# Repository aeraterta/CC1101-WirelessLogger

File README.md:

# Wireless Data Logging Platform for Human Temperature and Pulse Rate with Networked Mobile Nodes

<p align="center">

<p>

This is an undergraduate thesis made by Anthony E. Raterta as a requirement for the Degree Bachelor of Science in Electronics and Communications Engineering. 

## Objectives

Generally, the main objective of this study is to construct a prototype of a wireless multi-node data logger that has mobile sensor nodes using transceivers that communicate in the ISM band.

The following are the specific objectives of this study:

1.	To construct a wearable data logger platform.
2.	To utilize the CC1101 transceiver chips for communication.
3.	To attach a temperature and pulse rate sensor in the data logger platform for monitoring human body temperature and pulse rate. 
4.	To identify a suitable location for human body temperature and pulse rate monitoring.

## Methods 

### Flow

The operation of the system imposed is shown in the image below. It contains simplified illustration of the two major parts, the mobile sensor node which may be of any number but for the study, the researcher only made two nodes. The other major part of the system is the receiver node which receives the packets sent by both sensor nodes and dummy nodes.

<p align="center">

<p>

### Block Diagram

Shown in the image below is the physical architecture of the system designed to gather temperature and pulse rate of a patient at an interval set. A single sensor node is composed of an MLX90614 infrared thermometer and an infrared based Grove ear-clip pulse rate sensor.  These modules serve as input devices to an ATmega328p microcontroller unit with a CC1101 RF transceiver working at 433 mega hertz frequency band connected into it and to have the data gathered transmitted into the receiver node which is composed of a CC1101 RF transceiver, an Arduino UNO and a personal computer or a laptop. The microcontroller unit serves as a bridge to have the gathered data stored into the PC or the database pool.

<p align="center">

<p>

### Materials:

1. MCU - For the device, a programmable ATmega328p microcontroller will be used to do the tasks set. The circuit of an Arduino UNO will be used since its circuit is free and its programming IDE is open source. Also, several supports and forums are available online which would be a great help for the study and could minimize the period of the over-all development process. However, some parts of the Arduino UNO are not usable for the hardware design and may be deemed unnecessary so these parts will be disregarded. Also, the ATmega328p working at 3.3 volts  in the Arduino UNO can also be set to use its internal 8 MHz clock which could be a great option in the aim of minimizing the size of the output device.

2. [MLX90614 Infrared Thermometer](https://www.melexis.com/en/documents/documentation/datasheets/datasheet-mlx90614) - A non-contact MLX90614 Infrared Thermometer working at voltage range of 2.4 – 3.6 volts will be used for the sensor node to gather temperature in degrees Celsius (°C). MLX90614 is best in medical usage with an accuracy of 0.5 degrees Celsius (°C).

3. [Grove Ear-Clip Heart Pulse Sensor](https://wiki.seeedstudio.com/Grove-Ear-clip_Heart_Rate_Sensor/) - The Grove ear-clip pulse sensor is an infrared based sensor that could detect the changes in the density of blood due to the occurrence of pulse during blood circulations. By determining the time interval of the changes of the blood density in the ear lobe, the sensor can have an accurate value of pulse rate.

4. [CC1101 RF Transceiver](http://www.ti.com/lit/ds/symlink/cc1101.pdf?ts=1590260097931) - To maximize the mobility of the sensor node, the transmission of the data gathered from the sensors can be sent wirelessly depending on the choice of media. The effective transmission range for such media should also be maximized so that a bigger scope of a network will be made without jeopardizing the aim of minimizing the power consumption of each component used in the device. To cater such considerations, a CC1101 RF transceiver operating at 433 MHz was used. The said transceiver is capable of naming each node with a specific unique address which is beneficial for the study. A CC1101 RF transceiver break-out module will be used in the early development of the device for testing and debugging purposes. 

5. [Power Supply](https://github.com/aeraterta/CC1101-WirelessLogger/tree/master/Design/ADI-sepic-boost-converter) - The devices uses the ADP1621 SEPIC Converter which supplies a constant 3.3 volts output despite the diminishing value of input voltage ranging from 5 – 3 volts. Such circuit is ideal for mobile data loggers because of its capability of regulating and boosting input voltages.

6. Power Source - Since the main power supply needed for the device needs input voltage ranging from 3 to 5 volts, a mobile phone battery is a good option for such application. 

## Device

### PCB Layout Plan

<p align="center">

<p>

### PCB Layout vs Actual

###### Mobile Node

<p align="center">

<p>

###### Receiver Node

<p align="center">

<p>

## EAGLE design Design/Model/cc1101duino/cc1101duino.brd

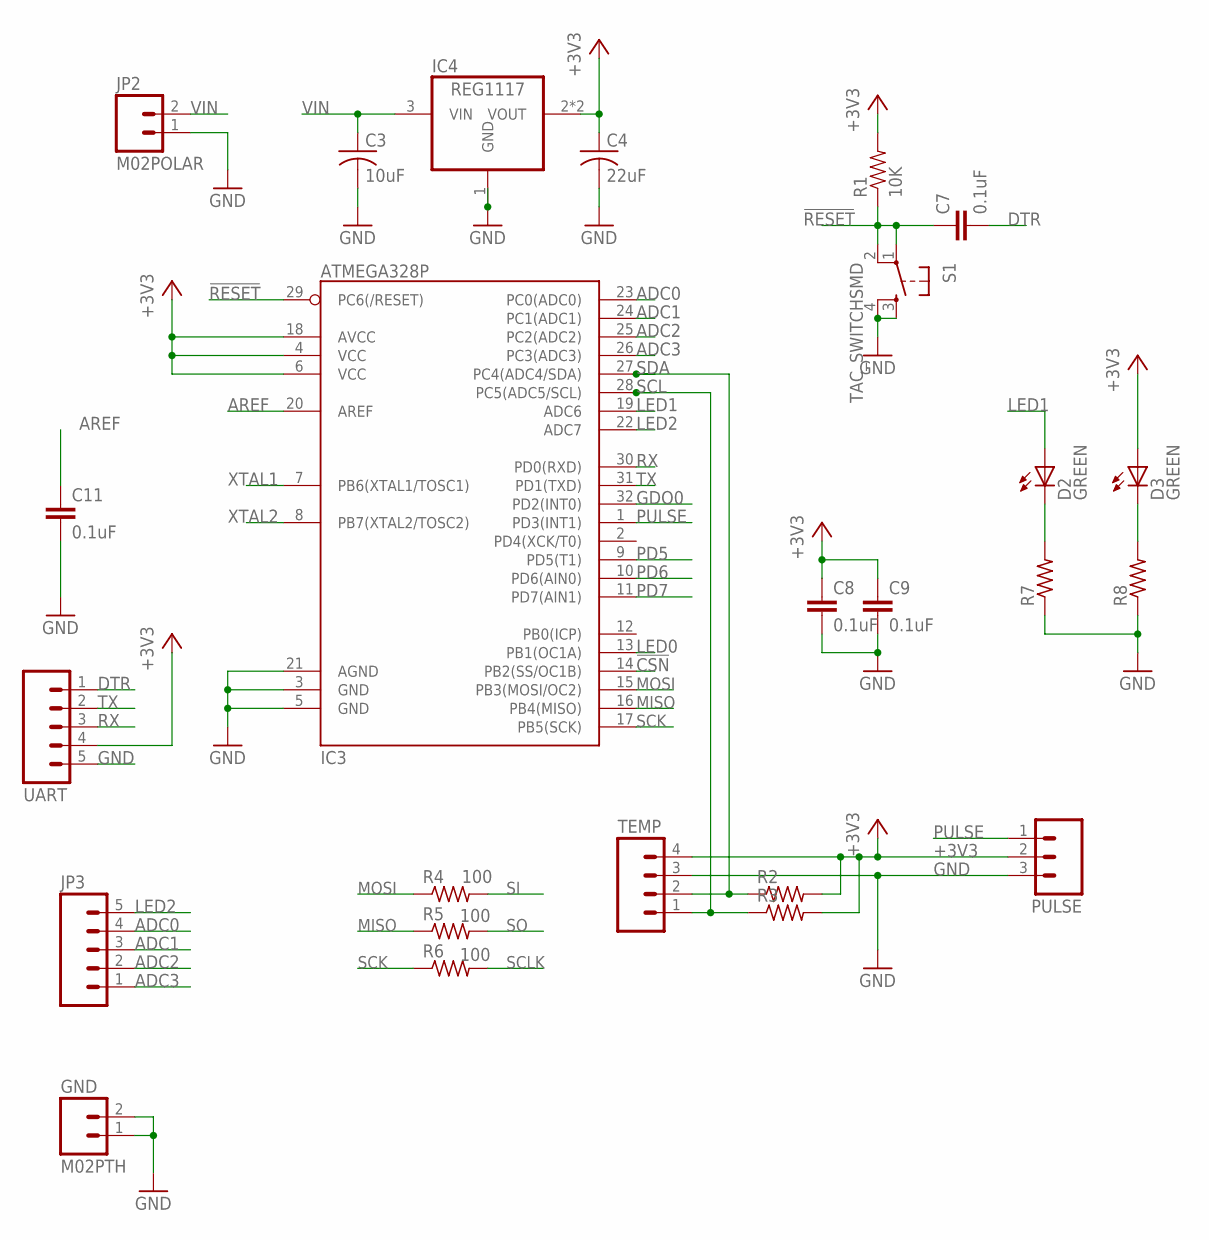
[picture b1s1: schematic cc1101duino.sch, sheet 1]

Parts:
C3: 10uF; C0805; MPN 06034D106MAT2A
C4: 22uF; C0805; MPN 06034D106MAT2A
C7, C8, C9, C11: 0.1uF; 0805
D2, D3: GREEN; LED-0603
GND: M02PTH; 1X02
IC3: ATMEGA328P; TQFP32-08
IC4: REG1117; SOT223
JP2: M02POLAR; MOLEX-1X2
JP3: M05PTH; 1X05
PULSE: M03POLAR; MOLEX-1X3
R1: 10K; 0603-RES
R2, R3: R-US_R0805; R0805
R4, R5, R6: 100; R0603
R7, R8: R-US_R0603; R0603
S1: TAC_SWITCHSMD; TACTILE-SWITCH-SMD
TEMP: M04POLAR; MOLEX-1X4
UART: M05PTH; 1X05

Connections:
!CSN: IC3.14 (PB2(SS/OC1B)); also elsewhere on the board
!RESET: C7.1, IC3.29 (PC6(/RESET)), R1.1, S1.1, S1.2
+3V3: C4.1, C8.1, C9.1, D3.A, IC3.4 (VCC), IC3.6 (VCC), IC3.18 (AVCC), IC4.2 (VOUT), IC4.4 (VOUT), PULSE.2, R1.2, R2.2, R3.2, TEMP.4, UART.4; also elsewhere on the board
ADC0: IC3.23 (PC0(ADC0)), JP3.4
ADC1: IC3.24 (PC1(ADC1)), JP3.3
ADC2: IC3.25 (PC2(ADC2)), JP3.2
ADC3: IC3.26 (PC3(ADC3)), JP3.1
AREF: C11.1, IC3.20 (AREF)
DTR: C7.2, UART.1
GDO0: IC3.32 (PD2(INT0)); also elsewhere on the board
GND: C3.2, C4.2, C8.2, C9.2, C11.2, GND.1, GND.2, IC3.3 (GND), IC3.5 (GND), IC3.21 (AGND), IC4.1 (GND), JP2.1, PULSE.3, R7.1, R8.1, S1.3, S1.4, TEMP.3, UART.5; also elsewhere on the board
LED0: IC3.13 (PB1(OC1A))
LED1: D2.A, IC3.19 (ADC6)
LED2: IC3.22 (ADC7), JP3.5
MISO: IC3.16 (PB4(MISO)), R5.1; also elsewhere on the board
MOSI: IC3.15 (PB3(MOSI/OC2)), R4.1; also elsewhere on the board
unnamed: D2.C, R7.2
unnamed: D3.C, R8.2
PD5: IC3.9 (PD5(T1))
PD6: IC3.10 (PD6(AIN0))
PD7: IC3.11 (PD7(AIN1))
PULSE: IC3.1 (PD3(INT1)), PULSE.1
RX: IC3.30 (PD0(RXD)), UART.3
SCK: IC3.17 (PB5(SCK)), R6.1; also elsewhere on the board
SCL: IC3.28 (PC5(ADC5/SCL)), R3.1, TEMP.1
SCLK: R6.2; also elsewhere on the board
SDA: IC3.27 (PC4(ADC4/SDA)), R2.1, TEMP.2
SI: R4.2; also elsewhere on the board
SO: R5.2; also elsewhere on the board
TX: IC3.31 (PD1(TXD)), UART.2
VIN: C3.1, IC4.3 (VIN), JP2.2
XTAL1: IC3.7 (PB6(XTAL1/TOSC1))
XTAL2: IC3.8 (PB7(XTAL2/TOSC2))

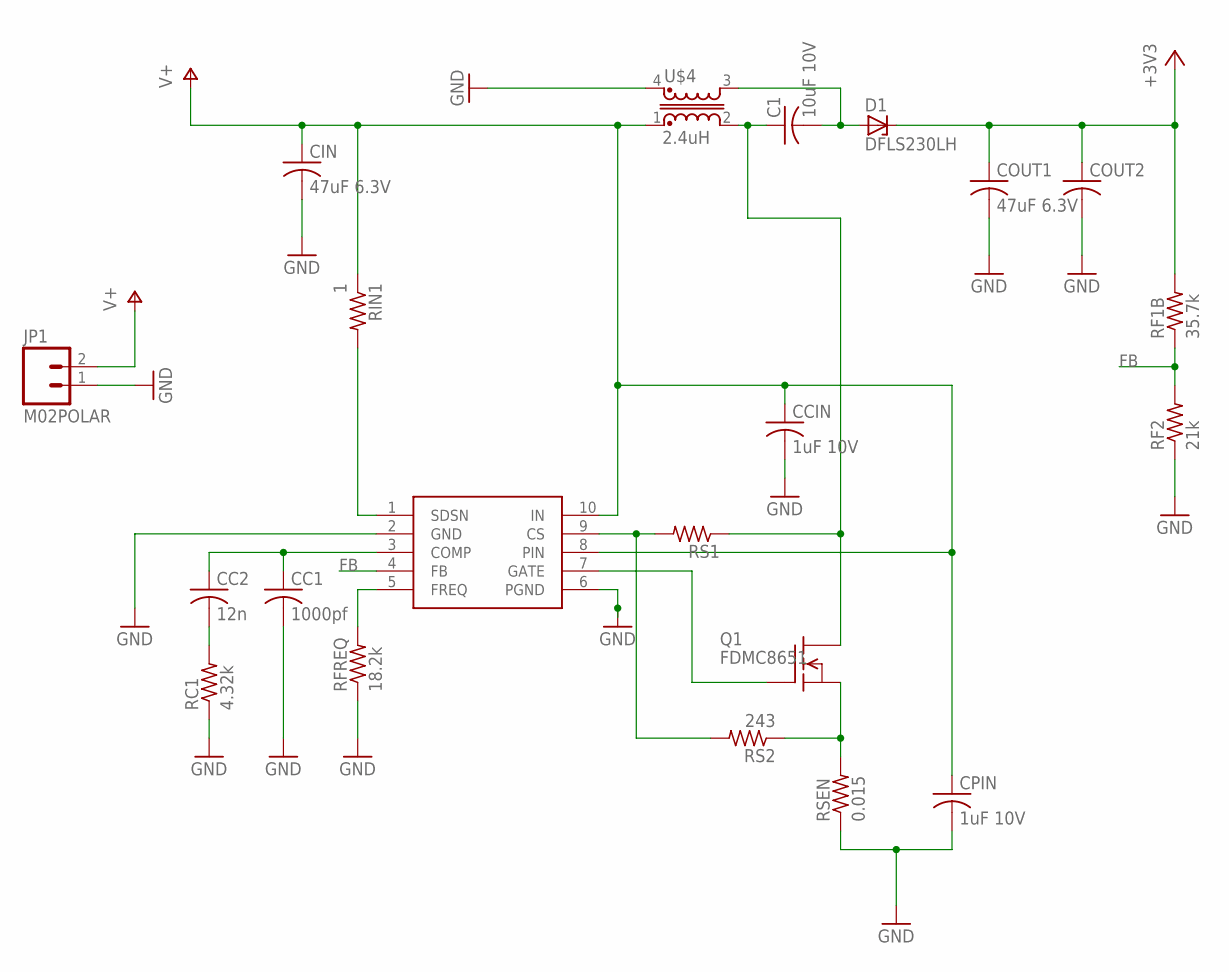
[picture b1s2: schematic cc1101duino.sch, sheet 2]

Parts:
C1: 10uF 10V; C0805K
CC1: 1000pf; C0805K
CC2: 12n; C0805K
CCIN: 1uF 10V; C0603K
CIN: 47uF 6.3V; C0805K
COUT1: 47uF 6.3V; C0805K
COUT2: C-USC0805K; C0805K
CPIN: 1uF 10V; C0603K
D1: DFLS230LH; DI123
JP1: M02POLAR; MOLEX-1X2
Q1: FDMC8651; PP8-3X3
RC1: 4.32k; R0805
RF1B: 35.7k; R0805
RF2: 21k; R0805
RFREQ: 18.2k; R0805
RIN1: 1; R0805
RS1: R-US_R0805; R0805
RS2: 243; R0805
RSEN: 0.015; R0805
U$1: ADP1621; MSOP10
U$4: 2.4uH; INDUCTOR

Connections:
+3V3: COUT1.1, COUT2.1, D1.C, RF1B.2; also elsewhere on the board
C1: C1.2, D1.A, U$4.3 (2)
FB: RF1B.1, RF2.2, U$1.4 (FB)
GND: CC1.2, CCIN.2, CIN.2, COUT1.2, COUT2.2, CPIN.2, JP1.1, RC1.1, RF2.1, RFREQ.1, RSEN.1, U$1.2 (GND), U$1.6 (PGND), U$4.4 (1); also elsewhere on the board
unnamed: RFREQ.2, U$1.5 (FREQ)
unnamed: RIN1.2, U$1.1 (SDSN)
unnamed: Q1.1 (S), Q1.2 (S), Q1.3 (S), RS2.1, RSEN.2
unnamed: RS1.2, RS2.2, U$1.9 (CS)
unnamed: Q1.4 (G), U$1.7 (GATE)
unnamed: CC1.1, CC2.1, U$1.3 (COMP)
unnamed: CC2.2, RC1.2
unnamed: C1.1, Q1.5 (D), Q1.6 (D), Q1.7 (D), Q1.8 (D), Q1.9 (D), RS1.1, U$4.2 (4)
V+: CCIN.1, CIN.1, CPIN.1, JP1.2, RIN1.1, U$1.8 (PIN), U$1.10 (IN), U$4.1 (3)

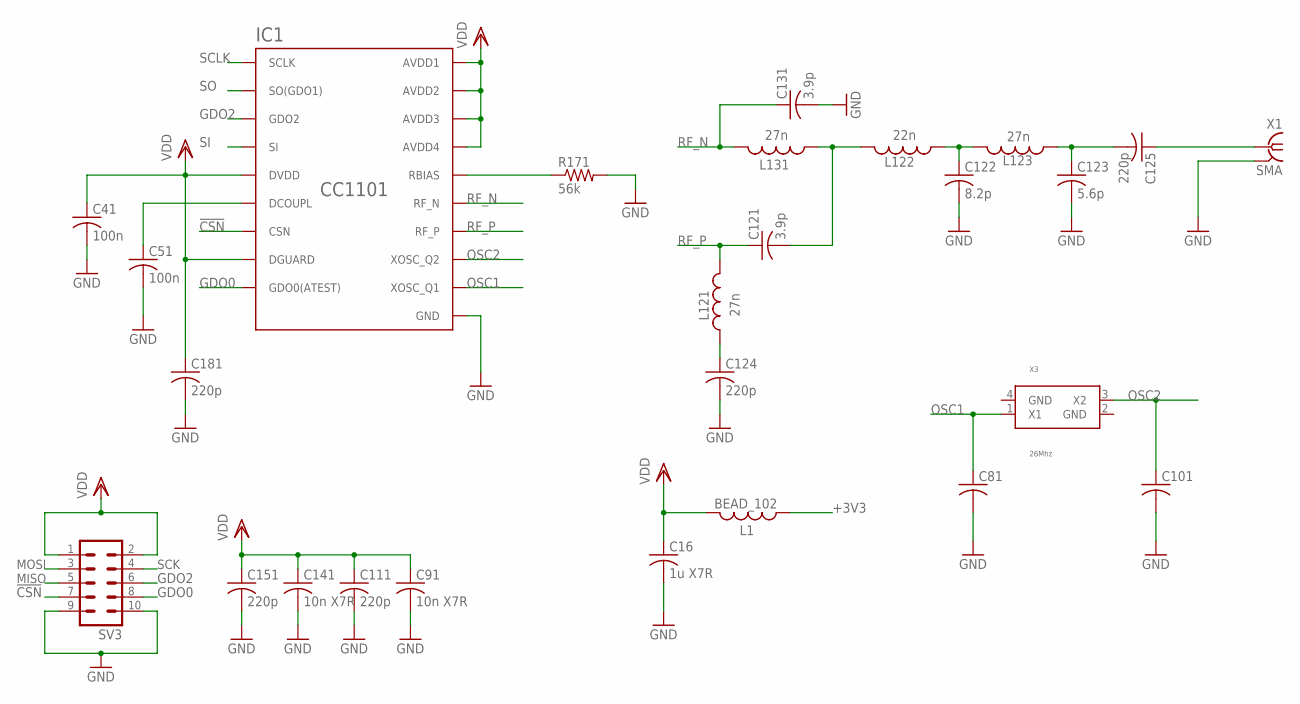
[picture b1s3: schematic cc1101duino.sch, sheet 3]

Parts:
C16: 1u X7R; C0805
C41, C51: 100n; C0402
C81, C101: C-USC0402; C0402
C91, C141: 10n X7R; C0402
C111, C124, C125, C151, C181: 220p; C0402
C121, C131: 3.9p; C0402
C122: 8.2p; C0402
C123: 5.6p; C0402
IC1: CC1101; QLP20
L1: BEAD_102; C0402
L121, L123, L131: 27n; C0402
L122: 22n; C0402
R171: 56k; R0402
SV3: MA05-2
X1: SMA; J502-ND-142-0711-821/826
X3: 26Mhz; ABM8G

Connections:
!CSN: IC1.7 (CSN), SV3.7; also elsewhere on the board
+3V3: L1.1; also elsewhere on the board
GDO0: IC1.6 (GDO0(ATEST)), SV3.8; also elsewhere on the board
GDO2: IC1.3 (GDO2), SV3.6
GND: C16.2, C41.2, C51.2, C81.2, C91.2, C101.2, C111.2, C122.2, C123.2, C124.2, C131.2, C141.2, C151.2, C181.2, IC1.16 (GND), IC1.19 (GND), IC1.GND, IC1.GND1 (GND), IC1.GND2 (GND), IC1.GND3 (GND), IC1.GND4 (GND), IC1.GND5 (GND), R171.2, SV3.9, SV3.10, X1.G@1 (2), X1.G@2 (2), X1.G@3 (2), X1.G@4 (2); also elsewhere on the board
MISO: SV3.5; also elsewhere on the board
MOSI: SV3.3; also elsewhere on the board
unnamed: C125.1, X1.1
unnamed: IC1.17 (RBIAS), R171.1
unnamed: C51.1, IC1.5 (DCOUPL)
unnamed: C121.2, L122.2, L131.1
unnamed: C124.1, L121.1
unnamed: C122.1, L122.1, L123.2
unnamed: C123.1, C125.2, L123.1
OSC1: C81.1, IC1.8 (XOSC_Q1), X3.1 (X1)
OSC2: C101.1, IC1.10 (XOSC_Q2), X3.3 (X2)
RF_N: C131.1, IC1.13 (RF_N), L131.2
RF_P: C121.1, IC1.12 (RF_P), L121.2
SCK: SV3.4; also elsewhere on the board
SCLK: IC1.1 (SCLK); also elsewhere on the board
SI: IC1.20 (SI); also elsewhere on the board
SO: IC1.2 (SO(GDO1)); also elsewhere on the board
VDD: C16.1, C41.1, C91.1, C111.1, C141.1, C151.1, C181.1, IC1.4 (DVDD), IC1.9 (AVDD1), IC1.11 (AVDD2), IC1.14 (AVDD3), IC1.15 (AVDD4), IC1.18 (DGUARD), L1.2, SV3.1, SV3.2

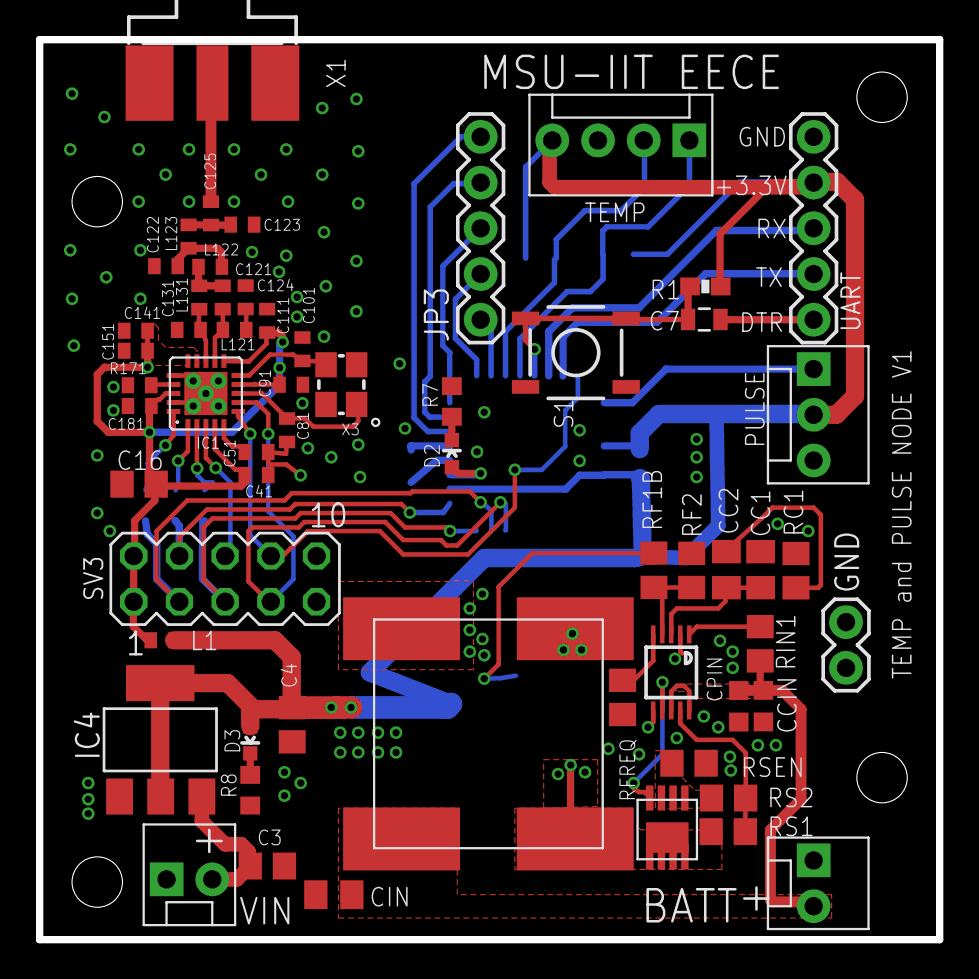
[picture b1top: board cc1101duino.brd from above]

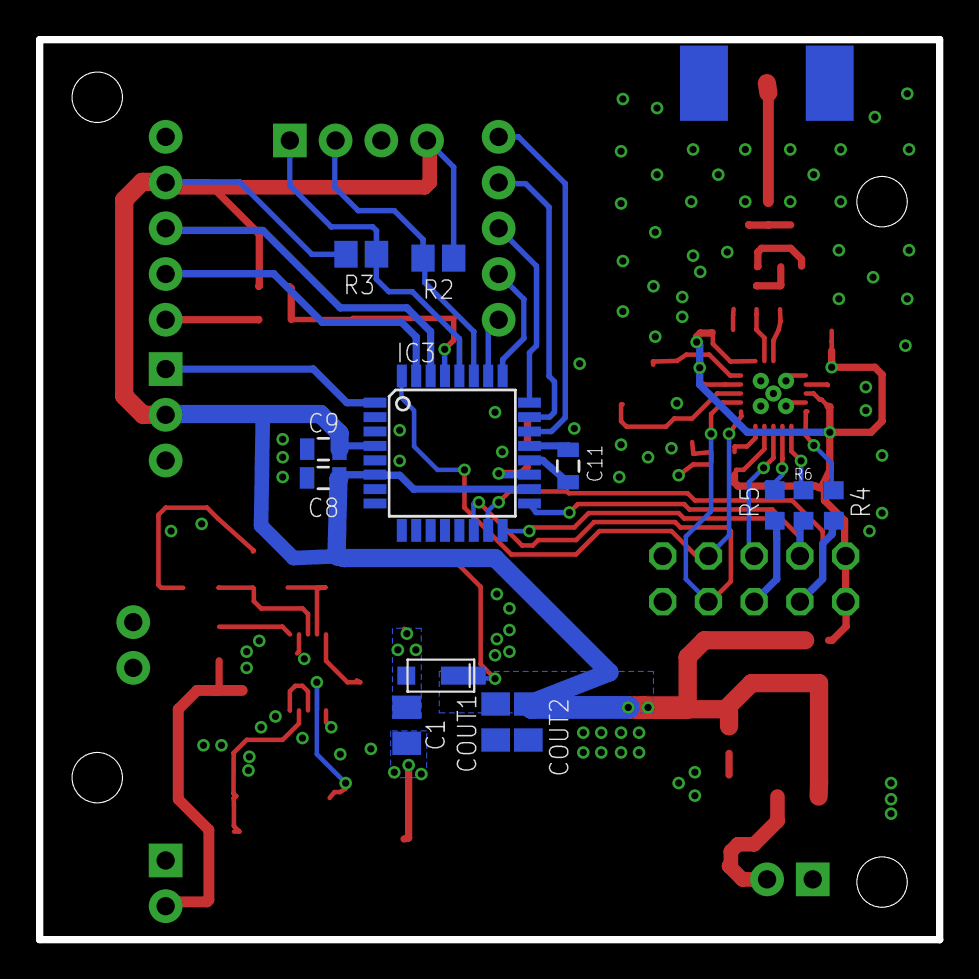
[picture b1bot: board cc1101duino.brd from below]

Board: 2 copper layers, 50.0 x 50.0 mm, 72 parts (13 on the bottom side), 51 nets.

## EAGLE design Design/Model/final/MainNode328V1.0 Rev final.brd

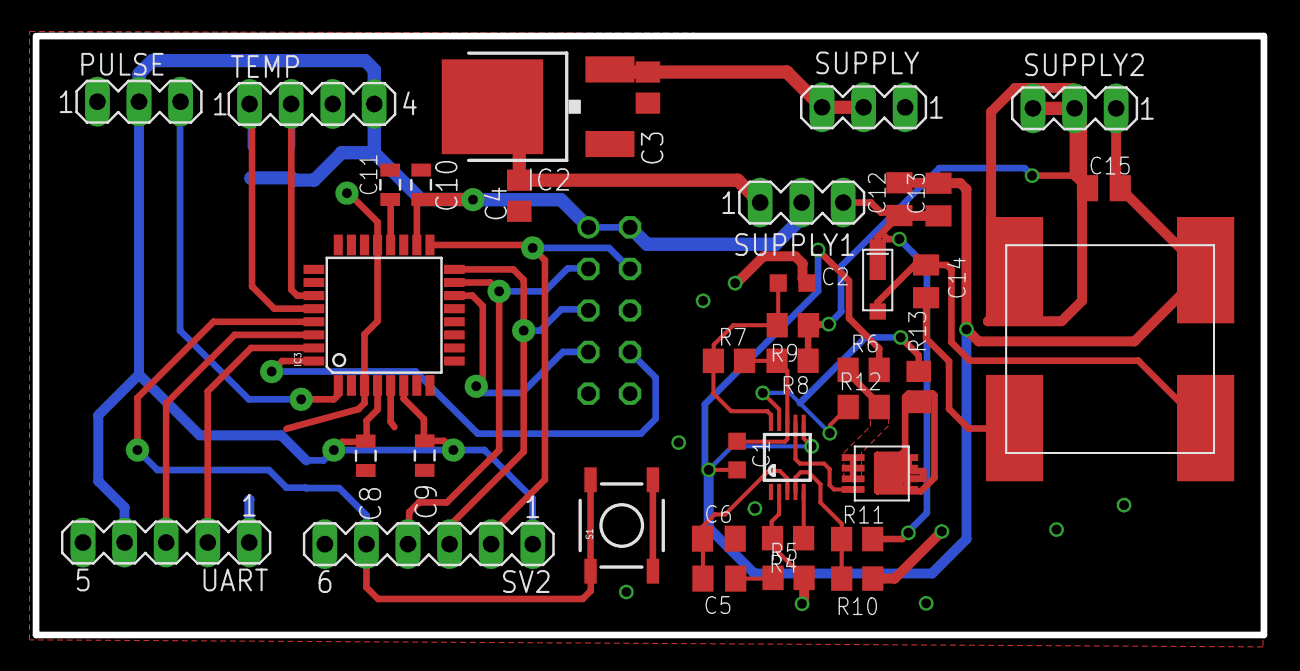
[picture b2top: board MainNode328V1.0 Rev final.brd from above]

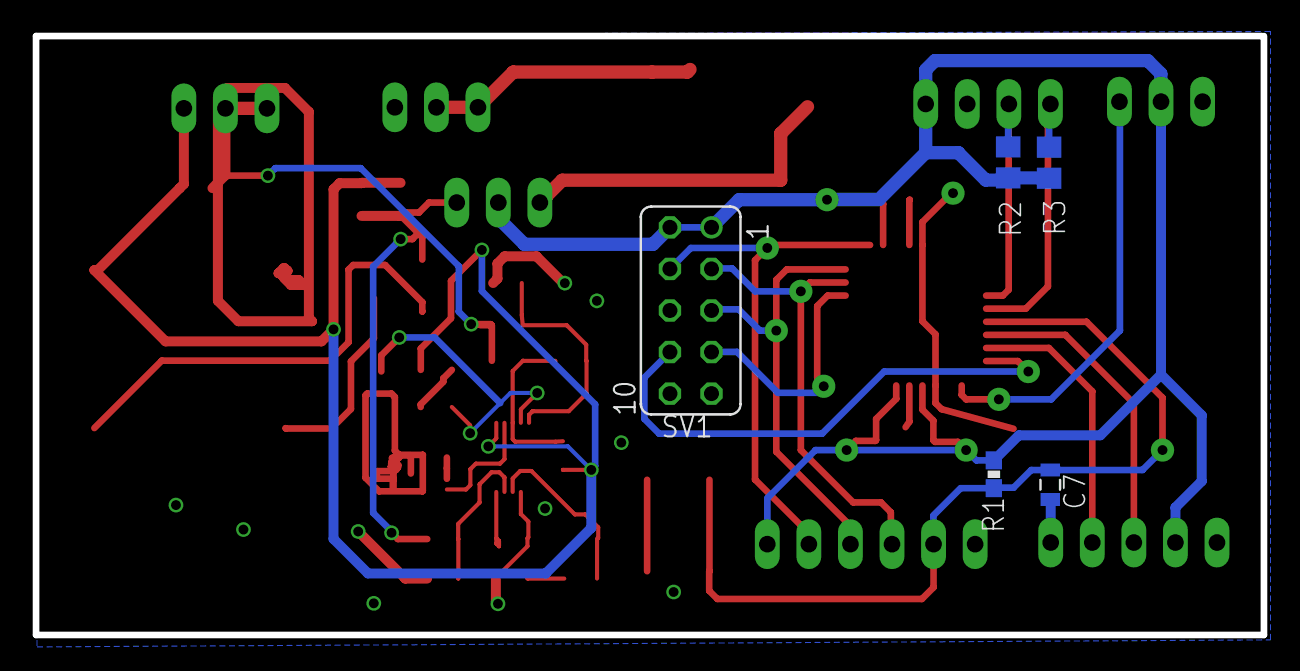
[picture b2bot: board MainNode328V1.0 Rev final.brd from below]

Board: 2 copper layers, 75.0 x 36.6 mm, 43 parts (5 on the bottom side), 32 nets.

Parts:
C1, C2: C0603K
C3: 10uF; C0805
C4: 22uF; C0805
C5, C6, C12, C13, C14, C15: C0805K
C7, C8, C9, C10, C11: 0.1uF; 0805
IC2: L1117; DPACK
IC3: ATMEGA328P; TQFP32-08
PULSE: MA03-1
R1: 10K; 0603-RES
R2, R3, R4, R5, R6, R7, R8, R9, R10, R11, R12, R13: R0805
S1: TAC_SWITCHSMD; TACTILE-SWITCH-SMD
SUPPLY, SUPPLY1, SUPPLY2: MA03-1
SV1: FE05-2
SV2: MA06-1
TEMP: MA04-1
U$1: ADP1621; MSOP10
U$2: DFLS230LH; DI123
U$3: FDMC8651; PP8-3X3
U$4: P0175NL; INDUCTOR
UART: MA05-1

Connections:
!CCSS: IC3.14, SV1.7
+3V3: C12.1, C13.1, R11.2, SUPPLY1.3, U$2.C
AGND: C1.2, C12.2, C13.2, C15.2, R6.1, SUPPLY2.1, U$1.6, U$4.4
AREF: C11.1, IC3.20
DTR: C7.2, UART.1
GDO0: IC3.32, SV1.8
GND: C2.2, C3.2, C4.2, C6.2, C8.2, C9.2, C10.2, C11.2, IC2.1, IC3.3, IC3.5, IC3.21, PULSE.1, R4.1, R5.1, R10.1, S1.3, S1.4, SUPPLY.1, SV1.9, SV1.10, SV2.6, TEMP.3, U$1.2, UART.5
MISO: IC3.16, SV1.5, SV2.3
MOSI: IC3.15, SV1.3, SV2.4
unnamed: R4.2, U$1.5
unnamed: C2.1, R7.2, R9.2, U$1.10
unnamed: C1.1, R7.1, R8.2, U$1.8
unnamed: R10.2, R11.1, U$1.4
unnamed: R6.2, R12.1, U$3.1, U$3.2, U$3.3
unnamed: R12.2, R13.2, U$1.9
unnamed: U$1.7, U$3.4
unnamed: R13.1, U$3.5, U$3.6, U$3.7, U$3.8, U$3.9
unnamed: C5.1, C6.1, U$1.3
unnamed: C5.2, R5.2
unnamed: C14.1, U$4.2
unnamed: C14.2, U$2.A, U$4.3
PULSE: IC3.1, PULSE.3
RESET: C7.1, IC3.29, R1.1, S1.1, S1.2, SV2.5
RX: IC3.30, UART.3
SCK: IC3.17, SV1.4, SV2.2
SCL: IC3.28, R3.1, TEMP.1
SDA: IC3.27, R2.1, TEMP.2
TX: IC3.31, UART.2
V+: C15.1, R8.1, R9.1, SUPPLY2.2, SUPPLY2.3, U$4.1
VCC: C8.1, C9.1, C10.1, IC3.4, IC3.6, IC3.18, PULSE.2, R1.2, R2.2, R3.2, SUPPLY1.2, SV1.1, SV1.2, SV2.1, TEMP.4, UART.4
VDD: C4.1, IC2.2, SUPPLY1.1
VIN: C3.1, IC2.3, SUPPLY.2, SUPPLY.3

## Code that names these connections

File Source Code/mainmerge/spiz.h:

/**
 * Copyright (c) 2011 Daniel Berenguer <dberenguer@usapiens.com>
 * 
 * This file is part of the panStamp project.
 * 
 * panStamp  is free software; you can redistribute it and/or modify
 * it under the terms of the GNU General Public License as published by
 * the Free Software Foundation; either version 2 of the License, or
 * any later version.
 * 
 * panLoader is distributed in the hope that it will be useful,
 * but WITHOUT ANY WARRANTY; without even the implied warranty of
 * MERCHANTABILITY or FITNESS FOR A PARTICULAR PURPOSE. See the
 * GNU General Public License for more details.
 * 
 * You should have received a copy of the GNU General Public License
 * along with panLoader; if not, write to the Free Software
 * Foundation, Inc., 51 Franklin St, Fifth Floor, Boston, MA  02110-1301 
 * USA
 * 
 * Author: Daniel Berenguer
 * Creation date: 03/03/2011
 */

#ifndef _SPI_H
#define _SPI_H

#include "Arduino.h"

/**
 * SPI pins
 */
#define SPI_SS   10     // PB0 = SPI_SS Pin_10
#define SPI_MOSI 11     // PB2 = MOSI Pin_11
#define SPI_MISO 12     // PB3 = MISO 
#define SPI_SCK  13     // PB1 = SCK
#define GDO0     2        // PD2 = INT0

#define PORT_SPI_MISO  PINB
#define BIT_SPI_MISO  4

#define PORT_SPI_SS  PORTB
#define BIT_SPI_SS   2

#define PORT_GDO0  PIND
#define BIT_GDO0  2

/**
 * Macros
 */
// Wait until SPI operation is terminated
#define wait_Spi()  while(!(SPSR & _BV(SPIF)))

/**
 * Class: SPI
 * 
 * Description:
 * Basic SPI class
 */
class SPI
{
  public:
    /**
     * init
     * 
     * SPI initialization
     */
    void init();

    /**
     * send
     * 
     * Send byte via SPI
     * 
     * 'value'  Value to be sent
     * 
     * Return:
     *  Response received from SPI slave
     */
    byte send(byte value);
};
#endif

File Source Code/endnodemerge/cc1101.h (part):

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#define CC1101_SIDLE             0x36        // Exit RX / TX, turn off frequency synthesizer and exit Wake-On-Radio mode if applicable
#define CC1101_SWOR              0x38        // Start automatic RX polling sequence (Wake-on-Radio) as described in Section 19.5 if
                                             // WORCTRL.RC_PD=0
#define CC1101_SPWD              0x39        // Enter power down mode when CSn goes high
#define CC1101_SFRX              0x3A        // Flush the RX FIFO buffer. Only issue SFRX in IDLE or RXFIFO_OVERFLOW states
#define CC1101_SFTX              0x3B        // Flush the TX FIFO buffer. Only issue SFTX in IDLE or TXFIFO_UNDERFLOW states
#define CC1101_SWORRST           0x3C        // Reset real time clock to Event1 value
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/**
 * CC1101 configuration registers
 */
#define CC1101_IOCFG2            0x00        // GDO2 Output Pin Configuration
#define CC1101_IOCFG1            0x01        // GDO1 Output Pin Configuration
#define CC1101_IOCFG0            0x02        // GDO0 Output Pin Configuration
#define CC1101_FIFOTHR           0x03        // RX FIFO and TX FIFO Thresholds
#define CC1101_SYNC1             0x04        // Sync Word, High Byte
#define CC1101_SYNC0             0x05        // Sync Word, Low Byte
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 * Settings optimized for low current consumption
 */

#define CC1101_DEFVAL_IOCFG2     0x29        // GDO2 Output Pin Configuration
#define CC1101_DEFVAL_IOCFG1     0x2E        // GDO1 Output Pin Configuration
#define CC1101_DEFVAL_IOCFG0     0x06        // GDO0 Output Pin Configuration
#define CC1101_DEFVAL_FIFOTHR    0x47        // RX FIFO and TX FIFO Thresholds
#define CC1101_DEFVAL_SYNC1      0xB5        // Synchronization word, high byte
#define CC1101_DEFVAL_SYNC0      0x47        // Synchronization word, low byte
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
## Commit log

2020-05-21 Added contents
2020-05-21 updated contents
2020-05-23 Added readme
2020-10-19 Updated links
2023-05-25 update for portfolio
2023-06-09 test commit to test github actions

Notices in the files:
Source Code/endnodemerge/cc1101.h:
Copyright (c) 2011 panStamp <contact@panstamp.com>
it under the terms of the GNU Lesser General Public License as published by
the Free Software Foundation; either version 3 of the License, or
any later version.
parts and their libraries:
SparkFun-DigitalIC: Licensing: CC v3.0 Share-Alike You are welcome to use this library for commercial purposes.
SparkFun-Retired: Licensing:Creative Commons ShareAlike 4.0 International - https://creativecommons.org/licenses/by-sa/4.0
